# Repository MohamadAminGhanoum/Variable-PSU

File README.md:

# Variable-PSU
i want to make a variable power supply that i can use to power electronics. I will make it so that the voltage is variable and the current is also variable.

## The final build is looking like this:

## DEMO:
https://www.youtube.com/shorts/KkizdfmzUhE

## Schematics:

## PCB:

I then had to add footprints which took quite some time, and i had to allign these footprints with LCSC electronics, where i would get the components. This took quite some time.

## PCB 3d model:

The voltmeter-ammeter should be connected to the voltmeter/ampmeter connector which can be seen in the pcb(I tried to find out how to show the connection of the voltmeter/ammeter display to the board in the pcb, but couldnt since i cannot show the wiring.)

The BOM:

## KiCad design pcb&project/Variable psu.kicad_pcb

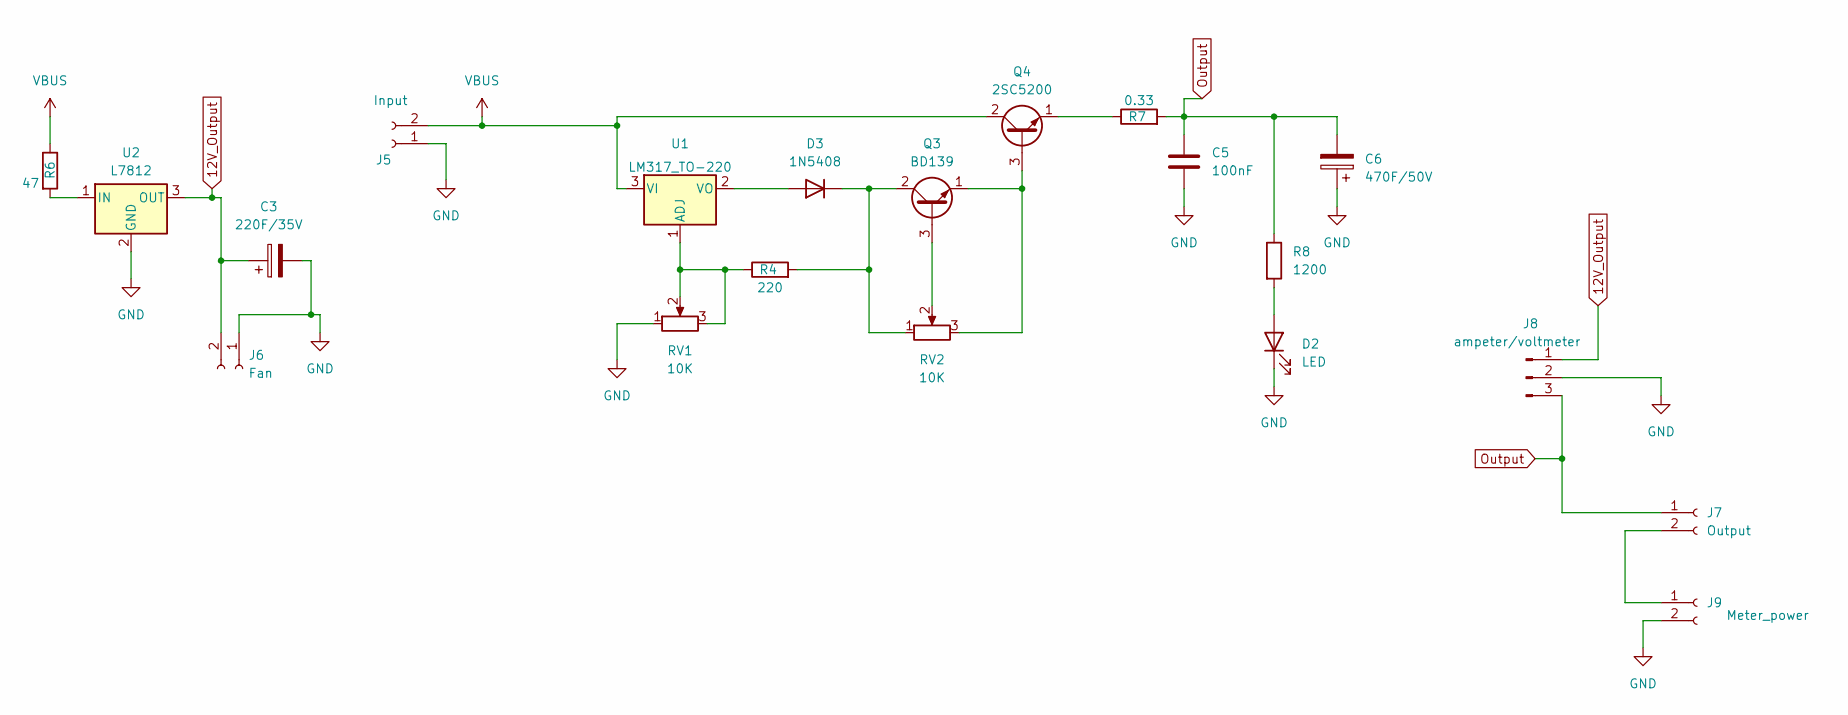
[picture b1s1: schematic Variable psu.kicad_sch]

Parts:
C3: 220F/35V; CP_Radial_D10.0mm_P5.00mm
C5: 100nF; C_Disc_D5.0mm_W2.5mm_P5.00mm
C6: 470F/50V; CP_Radial_D10.0mm_P5.00mm
D2: LED; LED_D3.0mm
D3: 1N5408; D_DO-201AD_P15.24mm_Horizontal
J5: Input; TerminalBlock_Phoenix_MKDS-1,5-2-5.08_1x02_P5.08mm_Horizont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
J6: Fan; TerminalBlock_Phoenix_MKDS-1,5-2-5.08_1x02_P5.08mm_Horizont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
J7: Output; TerminalBlock_Phoenix_MKDS-1,5-2-5.08_1x02_P5.08mm_Horizont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
J8: ampeter/voltmeter; TerminalBlock_Phoenix_MKDS-1,5-3-5.08_1x03_P5.08mm_Horizont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
J9: Meter_power; TerminalBlock_Phoenix_MKDS-1,5-2_1x02_P5.00mm_Horizontal
Q3: BD139; TO-126-3_Vertical
Q4: 2SC5200; TO-126-3_Vertical
R4: 220; R_Axial_DIN0207_L6.3mm_D2.5mm_P7.62mm_Horizontal
R6: 47; R_Axial_DIN0414_L11.9mm_D4.5mm_P15.24mm_Horizontal
R7: 0.33; R_Axial_DIN0414_L11.9mm_D4.5mm_P15.24mm_Horizontal
R8: 1200; R_Axial_DIN0309_L9.0mm_D3.2mm_P12.70mm_Horizontal
RV1, RV2: 10K; Potentiometer_Alps_RK09K_Single_Horizontal
U1: LM317_TO-220; TO-220-3_Vertical
U2: L7812; TO-220-3_Vertical

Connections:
12V_Output: C3.1, J6.2, J8.1, U2.3 (OUT)
GND: C3.2, C5.2, C6.1, D2.1 (K), J5.1, J6.1, J8.2, J9.2, RV1.1, U2.2 (GND)
unnamed: D2.2 (A), R8.2
unnamed: D3.2 (A), U1.2 (VO)
unnamed: D3.1 (K), Q3.2 (C), R4.2, RV2.1
unnamed: J7.2, J9.1
unnamed: Q3.3 (B), RV2.2
unnamed: Q3.1 (E), Q4.3 (B), RV2.3
unnamed: Q4.1 (E), R7.1
unnamed: R4.1, RV1.2, RV1.3, U1.1 (ADJ)
unnamed: R6.2, U2.1 (IN)
Output: C5.1, C6.2, J7.1, J8.3, R7.2, R8.1
VBUS: J5.2, Q4.2 (C), R6.1, U1.3 (VI)

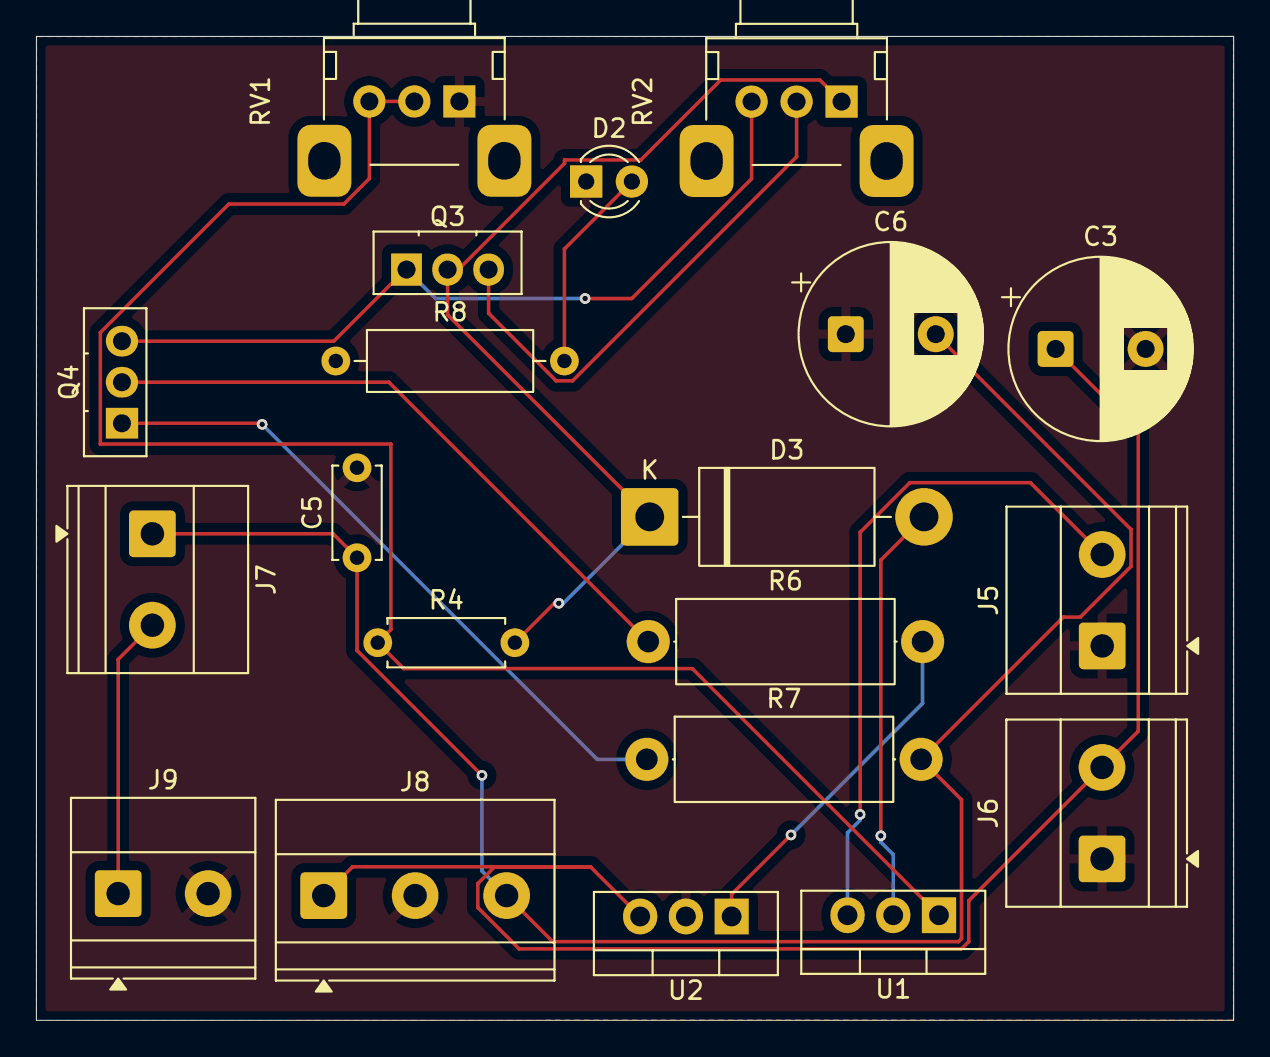
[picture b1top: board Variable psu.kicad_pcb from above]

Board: 2 copper layers, 66.5 x 54.7 mm, 20 parts (0 on the bottom side), 13 nets.

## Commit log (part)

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2026-01-10 Rename Screenshot 2026-01-05 at 14.08.55.png to assets/Screenshot 2026-01-05 at 14.08.55.png
2026-01-10 Rename PSUGerbers.zip to gerbers/PSUGerbers.zip
2026-01-10 Rename Variable psu.kicad_pro to pcb&project/Variable psu.kicad_pro
2026-01-23 Replace images with updated screenshots
    Updated image references in README with new screenshots.
2026-02-13 Update PSU BOM with voltmeter link
    Added a link to the voltmeter from Aliexpress.
2026-02-13 Update PSU BOM with voltmeter link and header
    Added a link for the voltmeter and updated the header.
2026-02-13 Update README with voltmeter-ammeter connection details
    Added details about the voltmeter-ammeter connection and included relevant images.
